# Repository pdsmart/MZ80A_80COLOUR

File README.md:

## Overview

The Sharp MZ80A was a personal computer from the 1980's and Sharp considered that a 40 column screen with 25 rows was sufficient for the home market. For most purposes it was sufficient but
with the rise of CP/M requiring 80 column displays there was a number of external vendors who provided add on boards to enhance the video capabilities. Most of these boards used bespoke
hardware solutions such as the addition of a 6845 CRT controller and non-standard Monitor ROMS.  A study of the MZ80A hardware though revealed it was identical to the more costly business
machine, the MZ80B. The hardware in the MZ80A had been wired differently to cripple its capabilities, presumably for marketing reasons, so by rerouting the wiring it is fairly easy to achieve
an 80 column display. This upgrade makes such a change, it removes the video controller gate arrays off the main board and reroutes the wiring on a daughter PCB to achieve 40/80 column
switched display.

Also, a study of the monitor ROM and the hardware indicates the MZ80A was intended to have a colour output board upgrade similar to the Sharp MZ700 but was never commercially sold.
[Nibbles Lab](http://retropc.net/ohishi/museum/mz1200.htm) spotted this and designed a circuit to upgrade the MZ80A so that it could output video to a colour monitor. Taking this base 
circuit with some modifications (composite video) I've added it into this upgrade. Also as the Character Generator ROM was raised onto the daughter PCB I took the opportunity to use a
modern Flash RAM and in so doing allow the storage and switching of multiple Character ROMS, ie. MZ80A, MZ700 I/II, Japanese MZ80K Rom etc. The 32KByte Flash RAM can store 16 character
generator ROM sets which can be switched via the attribute RAM (4 ROMS in 1 of 4 blocks) and the control register.

## MZ80A 40/80 Colour Board

The following pictures display v1.0 of the board. A few issues existed during production:-<br/>
1. The kicad footprint editor, probably my mistake, switched the 2 gate array footprints. Thus the gatearrays were in the wrong position which required a fair bit of fine soldering to correct.<br/>
2. The oscillator wasnt giving a clean signal so the addition of a 100pF ceramic cap between the U14B pin 4 and ground corrected this.<br/>
3. The gatearray G signal was not connected between the two gatearrays even though it was in the circuit, it appeared to be a PCB break.<br/>

I have corrected the circuit diagram and intend to produce a v1.1 PCB in due course. One area of the design I am not happy with is the enabling of 40/80 character mode and selection of the Character Generator ROM enable signal. Due to the limit of signals available to the board from the Video connector and gate array risers, I had to use the top 4 addresses of the video attribute RAM. It works but if you are using colour output you get the odd random colour if the top 4 bytes are being displayed (I initially thought these bytes wouldnt be displayed but the hardware scroll does display them). I am currently perfecting a latching mechanism such that the write to the top 4 bytes doesnt affect the attribute RAM. Also I will make the Flash RAM programmable in-situ such that a PCG is possible.

### Hardware

This portion is the colour generation circuit. Basically it adds a 2K Static RAM into the memory mapped location 0xD800 - 0xDFFF which is called the attribute RAM. The attribute RAM can be accessed by the CPU for read/write and the video circuitry will periodically scan each location,
both Character RAM and the new attribute RAM. As each byte is scanned by the video circuitry, its output is captured by IC U7 and used to generate a foreground and background colour signal according to the bits 6:4 (foreground) and 2:0 (background). Each bit pair 6+2, 5+1, 4+0 form the 3 basic colours, RGB
and each blended with the monochrome video signal to create the necessary RGB Video signal. The RGB is only digital, ie on/off, so a maximum of 8 colours foreground and 8 colours background can be generated. The actual colour seen on a monitor is controlled by the resistors R11:R19, R13:R1, R15:R17 and R20/R22. As RGB
on modern monitors is analogue, the voltage presented to the monitor via these resistor networks controls the colour. For Composite monitors, Q1 blends RGB and and composite Sync.

In addition to the colour generation circuit, IC15 on the motherboard, the Character Generator ROM, is lifted and replaced by IC U10, a 32KByte Flash RAM. Using bits 7 and 3 from the video attribute output stream of IC U7 and in combination with the latch IC U9, a Character Generator ROM set can be selected. The latch IC U9
selects a set of 4 out of 16 character generator sets within the 32KByte Flash RAM and the attribute bits allow subselection of the 4, thus each character can choose, via the attribute RAM, a possible 4 different character sets at any one time.

This portion is the 40/80 column character generation circuit. It is basically the same circuit as seen in the Sharp MZ80B. The Sharp MZ80A has the same chipset but it is wired differently, ie capped! Using this circuit, the chips are rewired and thus able to selectably switch between 40 and 80 character modes. Latch IC U9
provides the switching signal.

### Software

This is a hardware only project controlled by software which resides in the Rom Filing System or the SA-1510 monitor. The only 'soft' ware is the Character Generator ROM and also to know how to program the hardware.

All control is performed through the latch IC U9 at address location 0xDFFF. This address is used by the attribute RAM (it was deemed free when I started the project as it should appear off screen) so a write to this location *may* corrupt the attribute of the last character and only if it is visible whe the 
Character RAM is scrolled to the bottom.  The next release will resolve this bug by using a coded latch so that only a special write sequence will set the latch, other non-coded writes will go to the attribute RAM. This mechanism is needed because the Colour Board does not have access to the IORQ line or the upper
address lines so is limited to using the 0xD000:0xD7FF and 0xD800:0xDFFF chip selects.

The table below shows the bit functions of the IC U9 which is a 74HCT373 octal latch. Thus a switch from 40 to 80 column mode requires a write of 0x80 into the control address 0xDFFF.

| Bit | Function                 | Description           |
|-----|--------------------------|-----------------------|
|  0  | Character ROM Set Bit 0  | Select one of 4 sets of Character Generator ROMS.  |
|  1  | Character ROM Set Bit 1  |                       |
|  2  | Unused                   |                       |
|  3  | Unused                   |                       |
|  4  | Unused                   |                       |
|  5  | Unused                   |                       |
|  6  | Unused                   |                       |
|  7  | 40/80 Column Mode        | Enable 80 Column mode when set to 1, 40 Column when set to 0 (default) |

The Character Generator ROM on the Colour Board allows for upto 16 CG-ROM images to be stored and selected. On most of the MZ80 machines, the CG-ROM is 2K in size. On the MZ700/800 it is 4K in size. I havent yet obtained all the possible Sharp CG-ROM images so for the time being, the Character Generator
Flash RAM IC U10) is loaded as follows:

| Slot  | Attribute Bits 7,3 | U9 Latch Bits 0:1 | Size   | ROM                   | Description                          |
|-------|--------------------|-------------------|--------|-----------------------|--------------------------------------|
|  0    |       0,0          |       0,0         |  2K    | mz-80acg.rom          | MZ80A European CG-ROM                |
|  1    |       0,1          |       0,0         |  2K    | MZ80K_cgrom.rom       | MZ80K European CG-ROM                |
|  2    |       1,0          |       0,0         |  2K    | MZ80K2E_Jap_cgrom.rom | MZ80K Japanese CG-ROM                |
|  3    |       1,1          |       0,0         |  2K    | MZFONT.rom            | Unknown origin CG-ROM                |
| 4 & 5 |    0,0 - 0,1       |       0,1         |  4K    | MZ700_cgrom.rom       | MZ700 European CG-ROM (2 banks)      |
| 6 & 7 |    1,0 - 1,1       |       0,1         |  4K    | MZ700_cgrom_jp.rom    | MZ700 Japanese CG-ROM (2 banks)      |
|  8    |       0,0          |       1,0         |  2K    | mz-80acg.rom          | MZ80A European CG-ROM                |
|  9    |       0,1          |       1,0         |  2K    | MZ80B.rom             | MZ80B European CG-ROM                |
|  10   |       1,0          |       1,0         |  2K    | mz-80acg.rom          | MZ80A European CG-ROM                |
|  11   |       1,1          |       1,0         |  2K    | mz-80acg.rom          | MZ80A European CG-ROM                |
|  12   |       0,0          |       1,1         |  2K    | mz-80acg.rom          | MZ80A European CG-ROM                |
|  13   |       0,1          |       1,1         |  2K    | mz-80acg.rom          | MZ80A European CG-ROM                |
|  14   |       1,0          |       1,1         |  2K    | mz-80acg.rom          | MZ80A European CG-ROM                |
|  15   |       1,1          |       1,1         |  2K    | mz-80acg.rom          | MZ80A European CG-ROM                |

This image is created by the shell script in the repository, \[ABS PATH\]/software/tools/make_cgrom.sh and can be executed as follows:

````bash
cd [ABS PATH]/software
./tools/make_cgrom.sh
````

The output image, ie. ../../MZ80A_80COLOUR/software/roms/COLOURBOARD_CG.rom, can be directly flashed into a 28C256 Flash RAM and mounted on the Colour Board.

In order to set a colour on the colour output, an attribute byte is written into the attribute RAM for each character written to the Character RAM. The bits of the attribute RAM have the following function:

| Bit | Function              |
|-----|-----------------------|
|  0  | Background Blue       |
|  1  | Background Red        |
|  2  | Background Green      |
|  3  | Character ROM Bit 0   |
|  4  | Foreground Blue       |
|  5  | Foreground Red        |
|  6  | Foreground Green      |
|  7  | Character ROM Bit 1   |

To write a Blue character on a Black background for a character 'A' at screen position 0,0 - write 0x41 to Character RAM location 0xD000, write 0x10 to attribute RAM location 0xD800. This assumes Character Generator subset 0.

To select a Character Generator Set, the set is selected by bits 1:0 in IC U9 and the CG ROM, 1 of 4 is selected by the attribute bits 7 & 3 as per the table above.

### To Do
1. Correct control register access such that it doesnt write to attribute RAM.<br/>
2. Add additional logic to enable writes to the PCG Flash RAM.<br/>

## Credits

The original Colour circuit is copyright Nibbles Lab 2018 which was adapted for this design.  Where I have used or based any component on a 3rd parties design I have included the original authors copyright notice within the headers or given due credit. All 3rd party software, to my knowledge and research, is open source and freely useable, if there is found to be any component with licensing restrictions, it will be removed from this repository and a suitable link/config provided.

## Licenses

Not withstanding the Colour Module and any future limiting restrictions, this design, hardware and software, is licensed under the GNU Public Licence v3.

### The Gnu Public License v3
 The source and binary files in this project marked as GPL v3 are free software: you can redistribute it and-or modify it under the terms of the GNU General Public License as published by the Free Software Foundation, either version 3 of the License, or (at your option) any later version.

 The source files are distributed in the hope that it will be useful, but WITHOUT ANY WARRANTY; without even the implied warranty of MERCHANTABILITY or FITNESS FOR A PARTICULAR PURPOSE.  See the GNU General Public License for more details.

 You should have received a copy of the GNU General Public License along with this program.  If not, see http://www.gnu.org/licenses/.

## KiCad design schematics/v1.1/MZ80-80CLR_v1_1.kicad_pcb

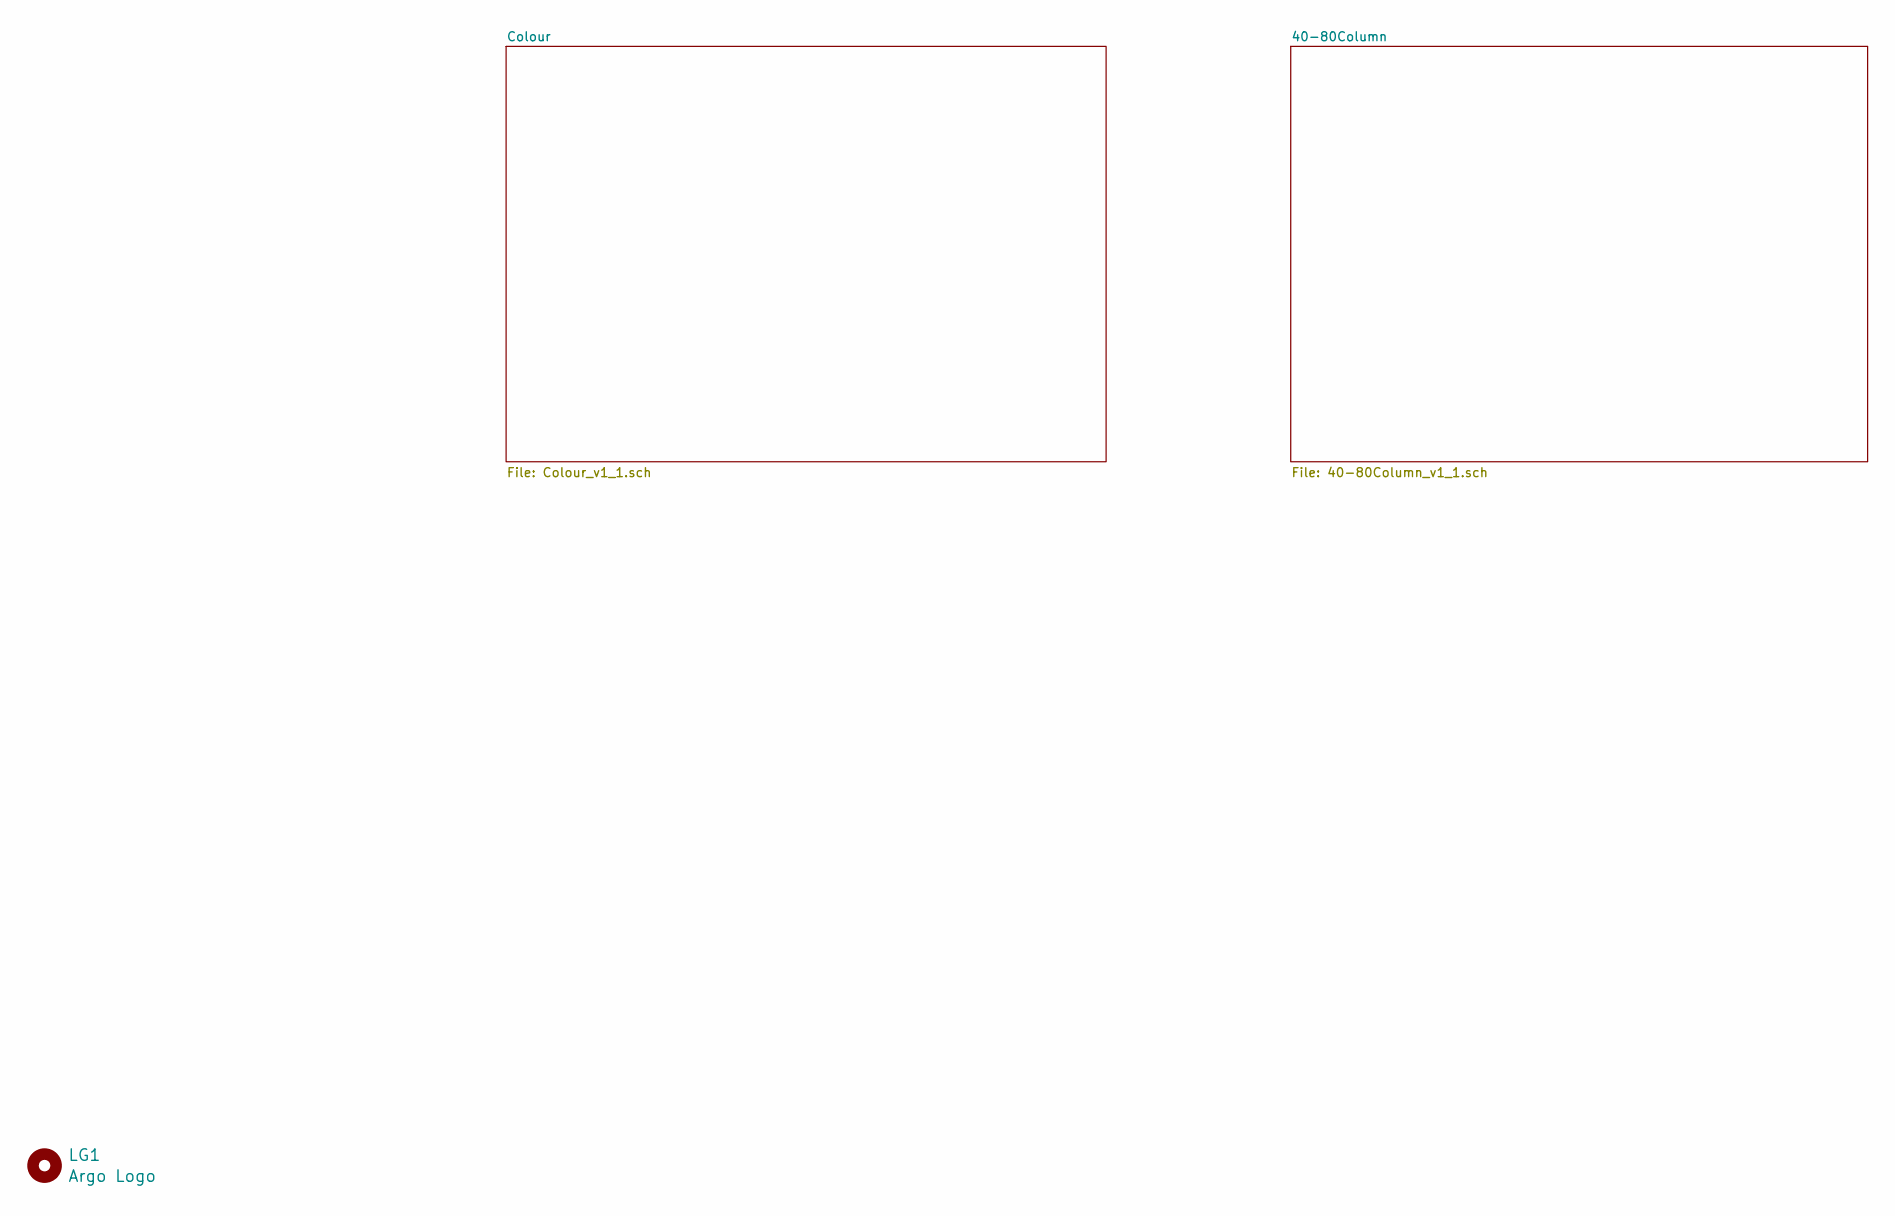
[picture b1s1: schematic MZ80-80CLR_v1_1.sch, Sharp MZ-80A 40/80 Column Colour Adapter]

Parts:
LG1: Argo Logo; Argo

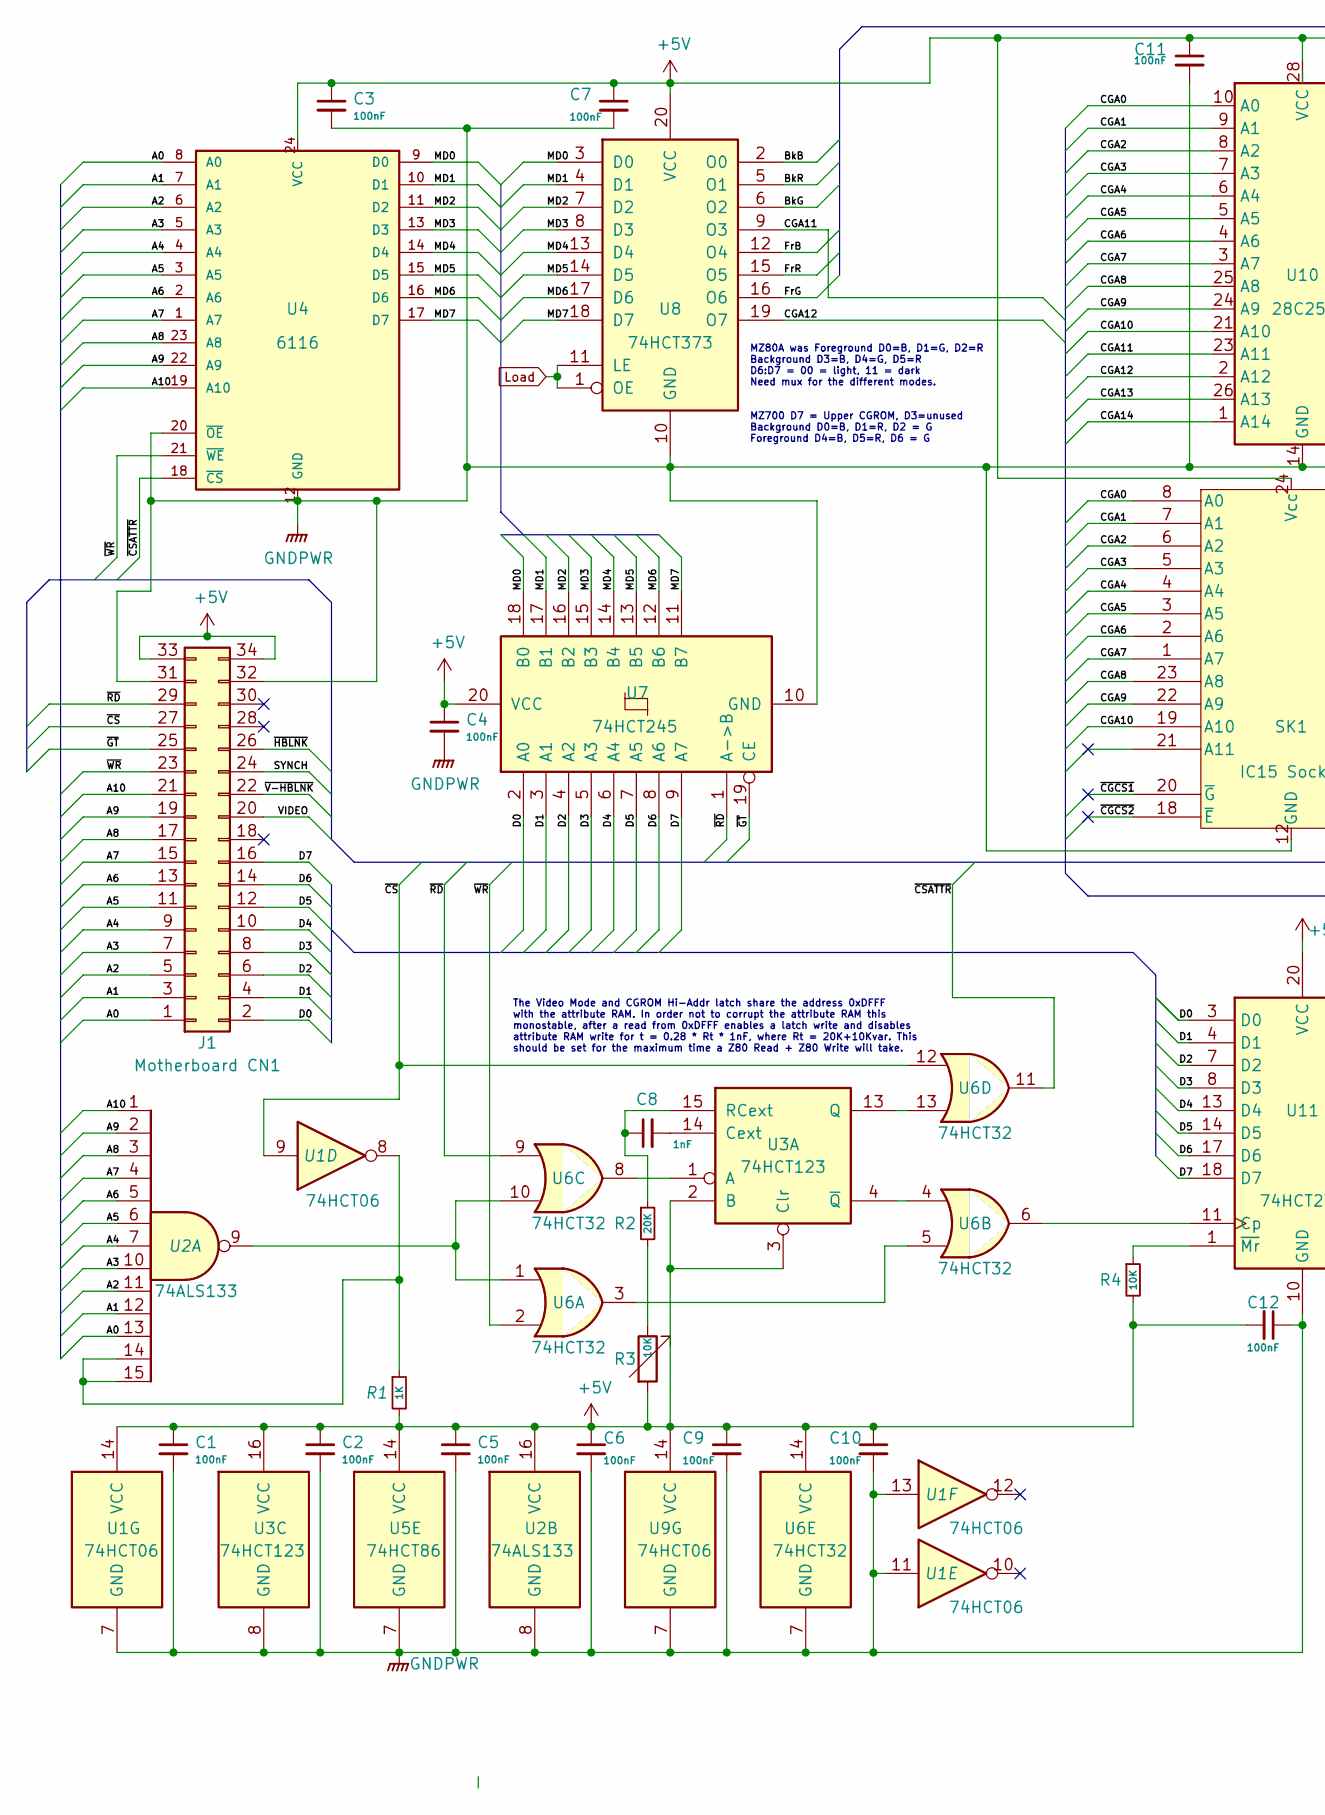
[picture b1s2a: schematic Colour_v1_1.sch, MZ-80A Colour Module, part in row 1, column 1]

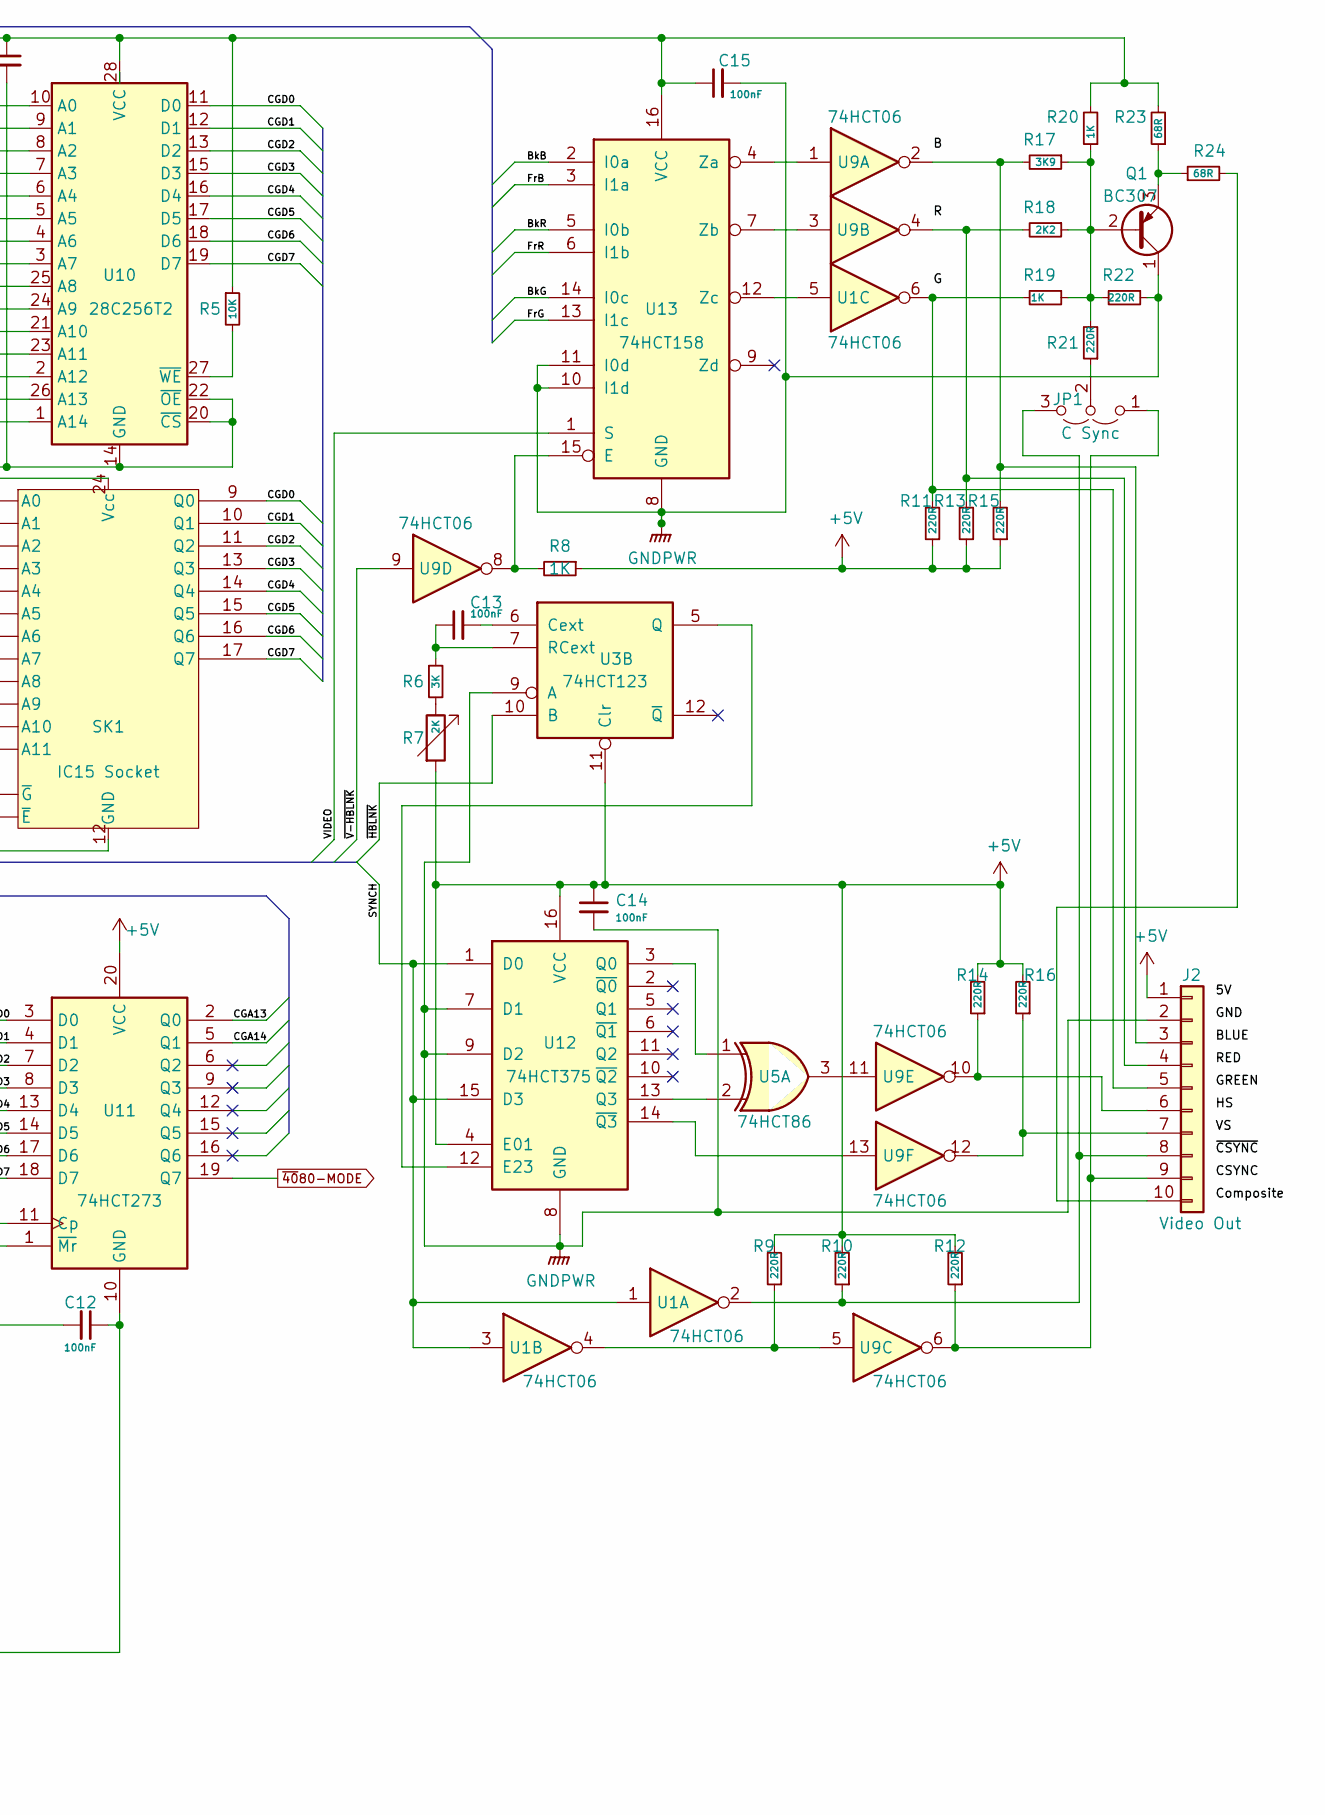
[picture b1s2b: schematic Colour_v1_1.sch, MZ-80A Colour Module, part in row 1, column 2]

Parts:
C1, C2, C3, C4, C5, C6, C7, C9, C10, C11, C12, C13, C14, C15: 100nF; C_0805_2012Metric_Pad1.15x1.40mm_HandSolder
C8: 1nF; C_0805_2012Metric_Pad1.15x1.40mm_HandSolder
J1: Motherboard CN1; PinSocket_2x17_P2.54mm_Vertical
J2: Video Out; PinSocket_1x10_P2.54mm_Vertical
JP1: C Sync; PinSocket_1x03_P2.00mm_Vertical
Q1: BC307; TO-92_Inline
R1, R8, R19, R20: 1K; R_0805_2012Metric_Pad1.15x1.40mm_HandSolder
R2: 20K; R_0805_2012Metric_Pad1.15x1.40mm_HandSolder
R3: 10K; Potentiometer_Bourns_3224W_Vertical
R4, R5: 10K; R_0805_2012Metric_Pad1.15x1.40mm_HandSolder
R6: 3K; R_0805_2012Metric_Pad1.15x1.40mm_HandSolder
R7: 2K; Potentiometer_Bourns_3224W_Vertical
R9, R10, R11, R12, R13, R14, R15, R16, R21, R22: 220R; R_0805_2012Metric_Pad1.15x1.40mm_HandSolder
R17: 3K9; R_0805_2012Metric_Pad1.15x1.40mm_HandSolder
R18: 2K2; R_0805_2012Metric_Pad1.15x1.40mm_HandSolder
R23, R24: 68R; R_0805_2012Metric_Pad1.15x1.40mm_HandSolder
SK1: IC15 Socket; DIP-24_W15.24mm_Socket
U1, U9: 74HCT06; SOIC-14_3.9x8.7mm_P1.27mm
U2: 74ALS133; SOIC-16_3.9x9.9mm_P1.27mm
U3: 74HCT123; SOIC-16_3.9x9.9mm_P1.27mm
U4: 6116; SOIC-24W_7.5x15.4mm_P1.27mm
U5: 74HCT86; SOIC-14_3.9x8.7mm_P1.27mm
U6: 74HCT32; SOIC-14_3.9x8.7mm_P1.27mm
U7: 74HCT245; SOIC-20W_7.5x12.8mm_P1.27mm
U8: 74HCT373; SOIC-20W_7.5x12.8mm_P1.27mm
U10: 28C256T2; DIP-28_W15.24mm
U11: 74HCT273; SOIC-20W_7.5x12.8mm_P1.27mm
U12: 74HCT375; SOIC-16_3.9x9.9mm_P1.27mm
U13: 74HCT158; SOIC-16_3.9x9.9mm_P1.27mm

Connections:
+5V: C1.1, C2.1, C3.1, C4.1, C5.1, C6.1, C7.1, C9.1, C10.1, C11.1, C12.2, C14.1, C15.1, J1.33, J1.34, J2.1, R1.2, R3.2, R4.2, R5.1, R7.2, R8.1, R9.2, R10.2, R11.1, R12.2, R13.1, R14.2, R15.1, R16.2, R20.2, R23.2, SK1.24 (Vcc), U1.14 (VCC), U2.16 (VCC), U3.2 (B), U3.3 (Clr), U3.11 (Clr), U3.16 (VCC), U4.24 (VCC), U5.14 (VCC), U6.14 (VCC), U7.20 (VCC), U8.20 (VCC), U9.14 (VCC), U10.28 (VCC), U11.20 (VCC), U12.4 (E01), U12.16 (VCC), U13.16 (VCC); also elsewhere on the board
/Colour/A0: J1.1, U2.13, U4.8 (A0)
/Colour/A1: J1.3, U2.12, U4.7 (A1)
/Colour/A2: J1.5, U2.11, U4.6 (A2)
/Colour/A3: J1.7, U2.10, U4.5 (A3)
/Colour/A4: J1.9, U2.7, U4.4 (A4)
/Colour/A5: J1.11, U2.6, U4.3 (A5)
/Colour/A6: J1.13, U2.5, U4.2 (A6)
/Colour/A7: J1.15, U2.4, U4.1 (A7)
/Colour/A8: J1.17, U2.3, U4.23 (A8)
/Colour/A9: J1.19, U2.2, U4.22 (A9)
/Colour/A10: J1.21, U2.1, U4.19 (A10)
/Colour/BkB: U8.2 (O0), U13.2 (I0a)
/Colour/BkG: U8.6 (O2), U13.14 (I0c)
/Colour/BkR: U8.5 (O1), U13.5 (I0b)
/Colour/CGA0: SK1.8 (A0), U10.10 (A0)
/Colour/CGA1: SK1.7 (A1), U10.9 (A1)
/Colour/CGA2: SK1.6 (A2), U10.8 (A2)
/Colour/CGA3: SK1.5 (A3), U10.7 (A3)
/Colour/CGA4: SK1.4 (A4), U10.6 (A4)
/Colour/CGA5: SK1.3 (A5), U10.5 (A5)
/Colour/CGA6: SK1.2 (A6), U10.4 (A6)
/Colour/CGA7: SK1.1 (A7), U10.3 (A7)
/Colour/CGA8: SK1.23 (A8), U10.25 (A8)
/Colour/CGA9: SK1.22 (A9), U10.24 (A9)
/Colour/CGA10: SK1.19 (A10), U10.21 (A10)
/Colour/CGA11: U8.9 (O3), U10.23 (A11)
/Colour/CGA12: U8.19 (O7), U10.2 (A12)
/Colour/CGA13: U10.26 (A13), U11.2 (Q0)
/Colour/CGA14: U10.1 (A14), U11.5 (Q1)
/Colour/CGD0: SK1.9 (Q0), U10.11 (D0)
/Colour/CGD1: SK1.10 (Q1), U10.12 (D1)
/Colour/CGD2: SK1.11 (Q2), U10.13 (D2)
/Colour/CGD3: SK1.13 (Q3), U10.15 (D3)
/Colour/CGD4: SK1.14 (Q4), U10.16 (D4)
/Colour/CGD5: SK1.15 (Q5), U10.17 (D5)
/Colour/CGD6: SK1.16 (Q6), U10.18 (D6)
/Colour/CGD7: SK1.17 (Q7), U10.19 (D7)
/Colour/D0: J1.2, U7.2 (A0), U11.3 (D0)
/Colour/D1: J1.4, U7.3 (A1), U11.4 (D1)
/Colour/D2: J1.6, U7.4 (A2), U11.7 (D2)
/Colour/D3: J1.8, U7.5 (A3), U11.8 (D3)
/Colour/D4: J1.10, U7.6 (A4), U11.13 (D4)
/Colour/D5: J1.12, U7.7 (A5), U11.14 (D5)
/Colour/D6: J1.14, U7.8 (A6), U11.17 (D6)
/Colour/D7: J1.16, U7.9 (A7), U11.18 (D7)
/Colour/FrB: U8.12 (O4), U13.3 (I1a)
/Colour/FrG: U8.16 (O6), U13.13 (I1c)
/Colour/FrR: U8.15 (O5), U13.6 (I1b)
/Colour/MD0: U4.9 (D0), U7.18 (B0), U8.3 (D0)
/Colour/MD1: U4.10 (D1), U7.17 (B1), U8.4 (D1)
/Colour/MD2: U4.11 (D2), U7.16 (B2), U8.7 (D2)
/Colour/MD3: U4.13 (D3), U7.15 (B3), U8.8 (D3)
/Colour/MD4: U4.14 (D4), U7.14 (B4), U8.13 (D4)
/Colour/MD5: U4.15 (D5), U7.13 (B5), U8.14 (D5)
/Colour/MD6: U4.16 (D6), U7.12 (B6), U8.17 (D6)
/Colour/MD7: U4.17 (D7), U7.11 (B7), U8.18 (D7)
/Colour/SYNCH: J1.24, U1.1, U1.3, U12.1 (D0), U12.15 (D3)
/Colour/VIDEO: J1.20, U13.1 (S)
/Colour/~CGCS1~: SK1.20 (~G)
/Colour/~CGCS2~: SK1.18 (~E)
/Colour/~CSATTR~: U4.18 (~CS), U6.11
/Colour/~CS~: J1.27, U1.9, U6.12
/Colour/~GT~: J1.25, U7.19 (CE)
/Colour/~HBLNK~: J1.26, U3.10 (B)
/Colour/~RD~: J1.29, U6.9, U7.1 (A->B)
/Colour/~V-HBLNK~: J1.22, U9.9
/Colour/~WR~: J1.23, U4.21 (~WE), U6.2
GNDPWR: C1.2, C2.2, C3.2, C4.2, C5.2, C6.2, C7.2, C9.2, C10.2, C11.2, C12.1, C14.2, C15.2, J1.31, J1.32, J2.2, Q1.1 (C), R22.1, SK1.12 (GND), U1.7 (GND), U1.11, U1.13, U2.8 (GND), U3.8 (GND), U3.9 (A), U4.12 (GND), U4.20 (~OE), U5.7 (GND), U6.7 (GND), U7.10 (GND), U8.10 (GND), U9.7 (GND), U10.14 (GND), U10.20 (~CS), U10.22 (~OE), U11.10 (GND), U12.7 (D1), U12.8 (GND), U12.9 (D2), U13.8 (GND), U13.10 (I1d), U13.11 (I0d); also elsewhere on the board
Load: U8.1 (OE), U8.11 (LE); also elsewhere on the board
unnamed: C8.1, R2.1, U3.15 (RCext)
unnamed: C8.2, U3.14 (Cext)
unnamed: C13.1, R6.1, U3.7 (RCext)
unnamed: C13.2, U3.6 (Cext)
unnamed: J2.3, R15.2, R17.2, U9.2
unnamed: J2.4, R13.2, R18.2, U9.4
unnamed: J2.5, R11.2, R19.2, U1.6
unnamed: J2.6, R14.1, U9.10
unnamed: J2.7, R16.1, U9.12
unnamed: J2.8, JP1.3 (B), R10.1, U1.2
unnamed: J2.9, JP1.1 (A), R12.1, U9.6
unnamed: J2.10, R24.2
unnamed: JP1.2 (C), R21.1
unnamed: Q1.2 (B), R17.1, R18.1, R19.1, R20.1, R21.2, R22.2
unnamed: Q1.3 (E), R23.1, R24.1
unnamed: R1.1, U1.8, U2.14, U2.15
unnamed: R2.2, R3.1
unnamed: R4.1, U11.1 (~Mr)
unnamed: R5.2, U10.27 (~WE)
unnamed: R6.2, R7.1
unnamed: R8.2, U9.8, U13.15 (E)
unnamed: R9.1, U1.4, U9.5
unnamed: U1.5, U13.12 (Zc)
unnamed: U2.9, U6.1, U6.10
unnamed: U3.1 (A), U6.8
unnamed: U3.4 (~Q), U6.4
unnamed: U3.13 (Q), U6.13
unnamed: U5.3, U9.11
unnamed: U6.3, U6.5
unnamed: U6.6, U11.11 (Cp)
unnamed: U5.1, U12.3 (Q0)
unnamed: U3.5 (Q), U12.12 (E23)
unnamed: U5.2, U12.13 (Q3)
unnamed: U9.13, U12.14 (~Q3)
unnamed: U9.1, U13.4 (Za)
unnamed: U9.3, U13.7 (Zb)
~40~80-MODE: U11.19 (Q7); also elsewhere on the board

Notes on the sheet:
MZ80A was Foreground D0=B, D1=G, D2=R Background D3=B, D4=G, D5=R D6:D7 = 00 = light, 11 = dark Need mux for the different modes.
MZ700 D7 = Upper CGROM, D3=unused Background D0=B, D1=R, D2 = G Foreground D4=B, D5=R, D6 = G
The Video Mode and CGROM Hi-Addr latch share the address 0xDFFF with the attribute RAM. In order not to corrupt the attribute RAM this monostable, after a read from 0xDFFF enables a latch write and disables attribute RAM write for t = 0.28 * Rt * 1nF, where Rt = 20K+10Kvar. This should be set for t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

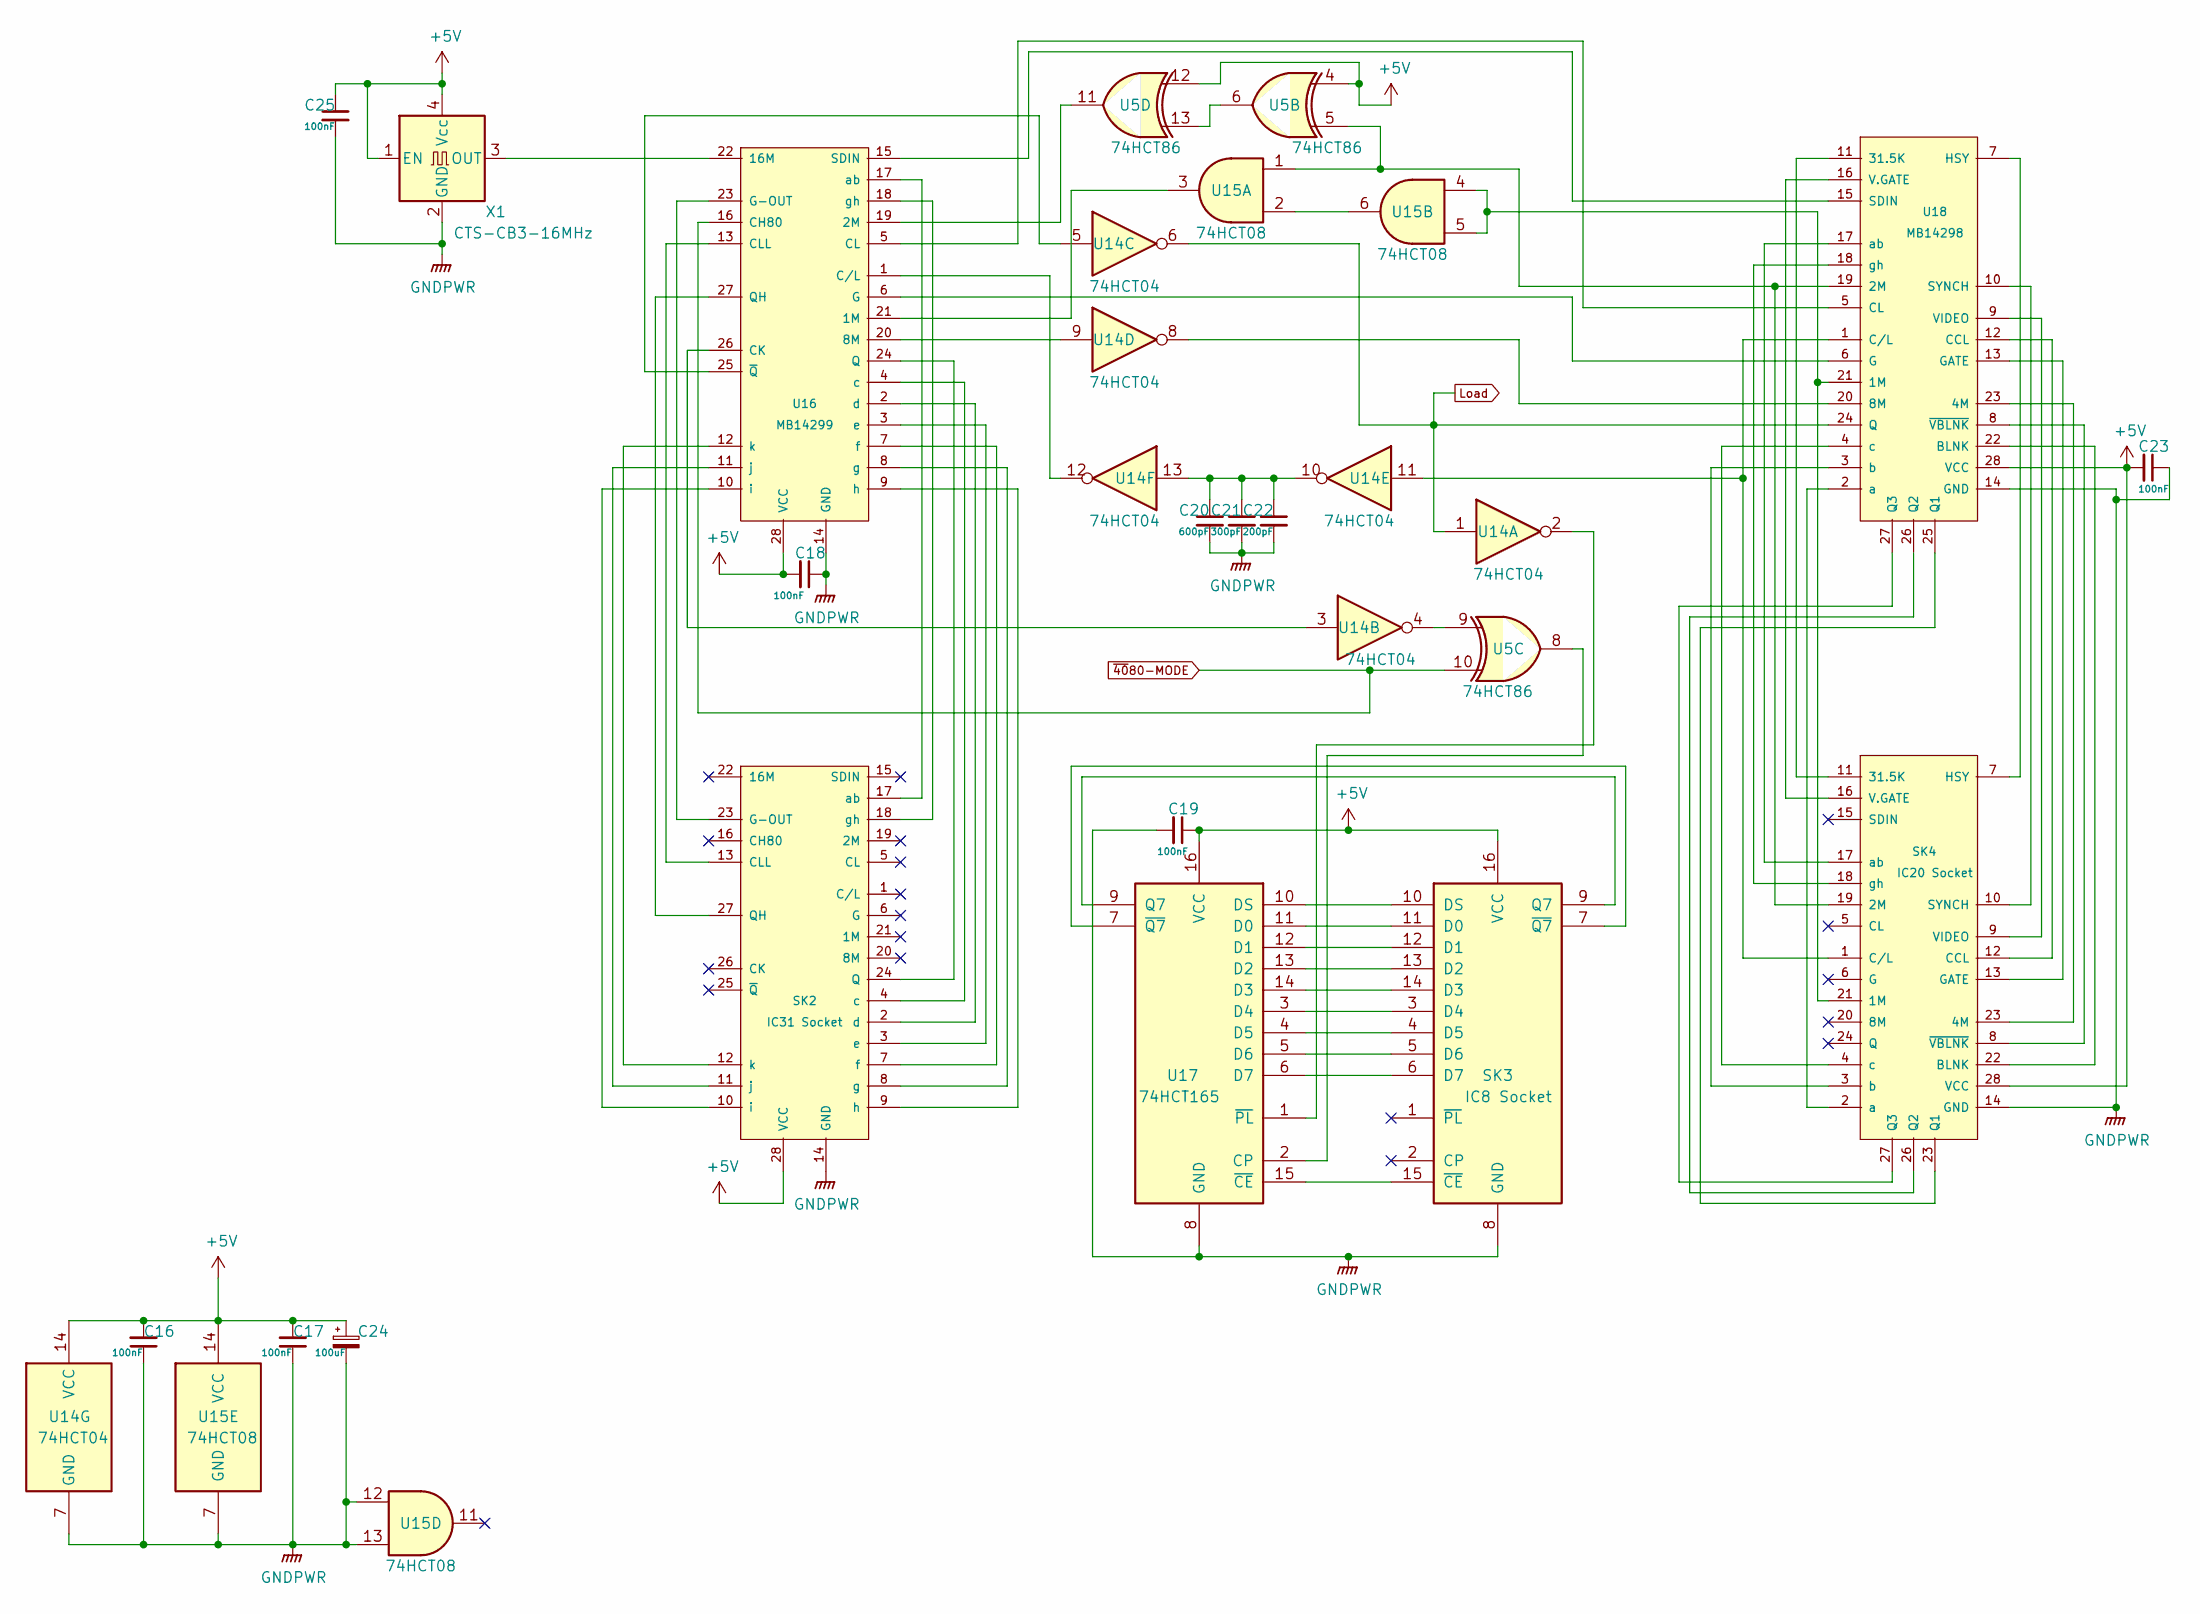
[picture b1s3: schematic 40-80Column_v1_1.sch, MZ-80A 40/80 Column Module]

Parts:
C16, C17, C18, C19, C23, C25: 100nF; C_0805_2012Metric_Pad1.15x1.40mm_HandSolder
C20: 600pF; C_0805_2012Metric_Pad1.15x1.40mm_HandSolder
C21: 300pF; C_0805_2012Metric_Pad1.15x1.40mm_HandSolder
C22: 200pF; C_0805_2012Metric_Pad1.15x1.40mm_HandSolder
C24: 100uF; C_1210_3225Metric_Pad1.42x2.65mm_HandSolder
SK2: IC31 Socket; DIP-28_W15.24mm_Socket
SK3: IC8 Socket; DIP-16_W7.62mm_Socket
SK4: IC20 Socket; DIP-28_W15.24mm_Socket
U5: 74HCT86; SOIC-14_3.9x8.7mm_P1.27mm
U14: 74HCT04; SOIC-14_3.9x8.7mm_P1.27mm
U15: 74HCT08; SOIC-14_3.9x8.7mm_P1.27mm
U16: MB14299; DIP-28_W15.24mm
U17: 74HCT165; SOIC-16_3.9x9.9mm_P1.27mm
U18: MB14298; DIP-28_W15.24mm
X1: CTS-CB3-16MHz; Oscillator_SMD_Abracon_ASE-4Pin_3.2x2.5mm

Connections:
+5V: C16.2, C17.2, C18.2, C19.1, C23.2, C24.1, C25.1, SK2.28 (VCC), SK3.16 (VCC), SK4.28 (VCC), U5.4, U5.12, U14.14 (VCC), U15.14 (VCC), U16.28 (VCC), U17.16 (VCC), U18.28 (VCC), X1.1 (EN), X1.4 (Vcc); also elsewhere on the board
GNDPWR: C16.1, C17.1, C18.1, C19.2, C20.2, C21.2, C22.2, C23.1, C24.2, C25.2, SK2.14 (GND), SK3.8 (GND), SK4.14 (GND), U14.7 (GND), U15.7 (GND), U15.12, U15.13, U16.14 (GND), U17.8 (GND), U18.14 (GND), X1.2 (GND); also elsewhere on the board
Load: U14.1, U14.6, U18.24 (Q); also elsewhere on the board
unnamed: C20.1, C21.1, C22.1, U14.10, U14.13
unnamed: SK2.2 (d), U16.2 (d)
unnamed: SK2.3 (e), U16.3 (e)
unnamed: SK2.4 (c), U16.4 (c)
unnamed: SK2.7 (f), U16.7 (f)
unnamed: SK2.8 (g), U16.8 (g)
unnamed: SK2.9 (h), U16.9 (h)
unnamed: SK2.10 (i), U16.10 (i)
unnamed: SK2.11 (j), U16.11 (j)
unnamed: SK2.12 (k), U16.12 (k)
unnamed: SK2.13 (CLL), U16.13 (CLL)
unnamed: SK2.17 (ab), U16.17 (ab)
unnamed: SK2.18 (gh), U16.18 (gh)
unnamed: SK2.23 (G-OUT), U16.23 (G-OUT)
unnamed: SK2.24 (Q), U16.24 (Q)
unnamed: SK2.27 (QH), U16.27 (QH)
unnamed: SK3.3 (D4), U17.3 (D4)
unnamed: SK3.4 (D5), U17.4 (D5)
unnamed: SK3.5 (D6), U17.5 (D6)
unnamed: SK3.6 (D7), U17.6 (D7)
unnamed: SK3.7 (~Q7), U17.7 (~Q7)
unnamed: SK3.9 (Q7), U17.9 (Q7)
unnamed: SK3.10 (DS), U17.10 (DS)
unnamed: SK3.11 (D0), U17.11 (D0)
unnamed: SK3.12 (D1), U17.12 (D1)
unnamed: SK3.13 (D2), U17.13 (D2)
unnamed: SK3.14 (D3), U17.14 (D3)
unnamed: SK3.15 (~CE), U17.15 (~CE)
unnamed: SK4.1 (C/L), U14.11, U18.1 (C/L)
unnamed: SK4.2 (a), U18.2 (a)
unnamed: SK4.3 (b), U18.3 (b)
unnamed: SK4.4 (c), U18.4 (c)
unnamed: SK4.7 (HSY), U18.7 (HSY)
unnamed: SK4.8 (~VBLNK~), U18.8 (~VBLNK~)
unnamed: SK4.9 (VIDEO), U18.9 (VIDEO)
unnamed: SK4.10 (SYNCH), U18.10 (SYNCH)
unnamed: SK4.11 (31.5K), U18.11 (31.5K)
unnamed: SK4.12 (CCL), U18.12 (CCL)
unnamed: SK4.13 (GATE), U18.13 (GATE)
unnamed: SK4.16 (V.GATE), U18.16 (V.GATE)
unnamed: SK4.17 (ab), U18.17 (ab)
unnamed: SK4.18 (gh), U18.18 (gh)
unnamed: SK4.19 (2M), U5.5, U15.1, U18.19 (2M)
unnamed: SK4.21 (1M), U15.4, U15.5, U18.21 (1M)
unnamed: SK4.22 (BLNK), U18.22 (BLNK)
unnamed: SK4.26 (Q2), U18.26 (Q2)
unnamed: SK4.27 (Q3), U18.27 (Q3)
unnamed: U5.6, U5.13
unnamed: U14.2, U17.1 (~PL)
unnamed: U14.3, U16.26 (CK)
unnamed: U5.9, U14.4
unnamed: U14.5, U16.25 (~Q~)
unnamed: U14.8, U18.20 (8M)
unnamed: U14.9, U16.20 (8M)
unnamed: U14.12, U16.1 (C/L)
unnamed: U15.2, U15.6
unnamed: U15.3, U16.21 (1M)
unnamed: U16.5 (CL), U18.5 (CL)
unnamed: U16.6 (G), U18.6 (G)
unnamed: U16.15 (SDIN), U18.15 (SDIN)
unnamed: U5.11, U16.19 (2M)
unnamed: U16.22 (16M), X1.3 (OUT)
unnamed: U5.8, U17.2 (CP)
~40~80-MODE: U5.10, U16.16 (CH80); also elsewhere on the board

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
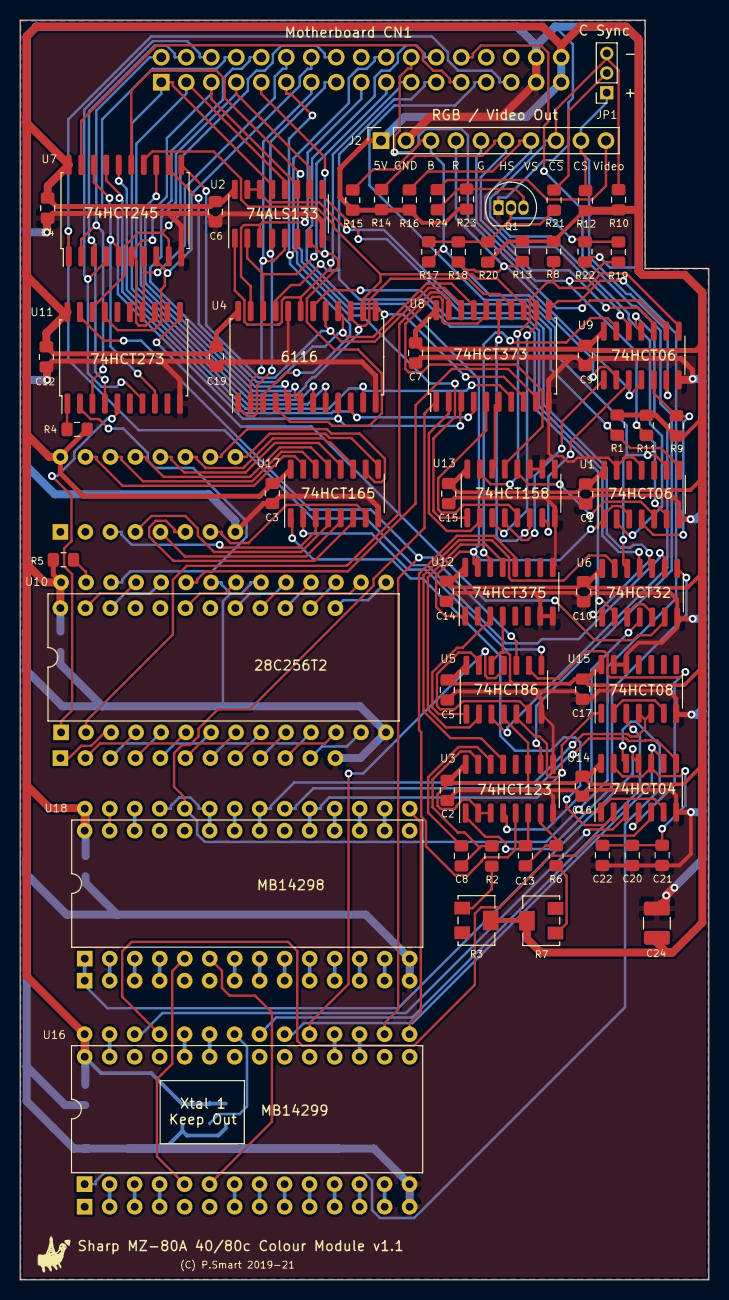
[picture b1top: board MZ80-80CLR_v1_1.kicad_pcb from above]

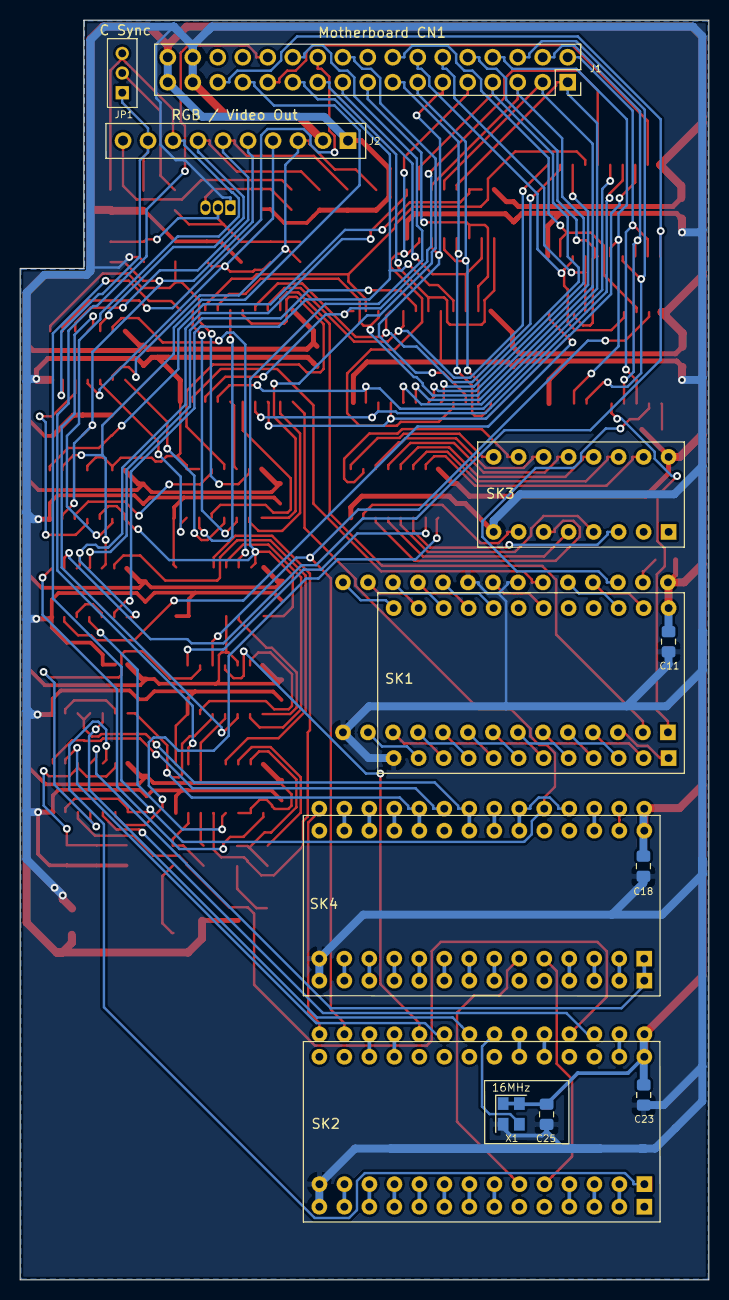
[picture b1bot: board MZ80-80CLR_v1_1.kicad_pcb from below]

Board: 2 copper layers, 70.0 x 128.0 mm, 77 parts (6 on the bottom side), 169 nets.
